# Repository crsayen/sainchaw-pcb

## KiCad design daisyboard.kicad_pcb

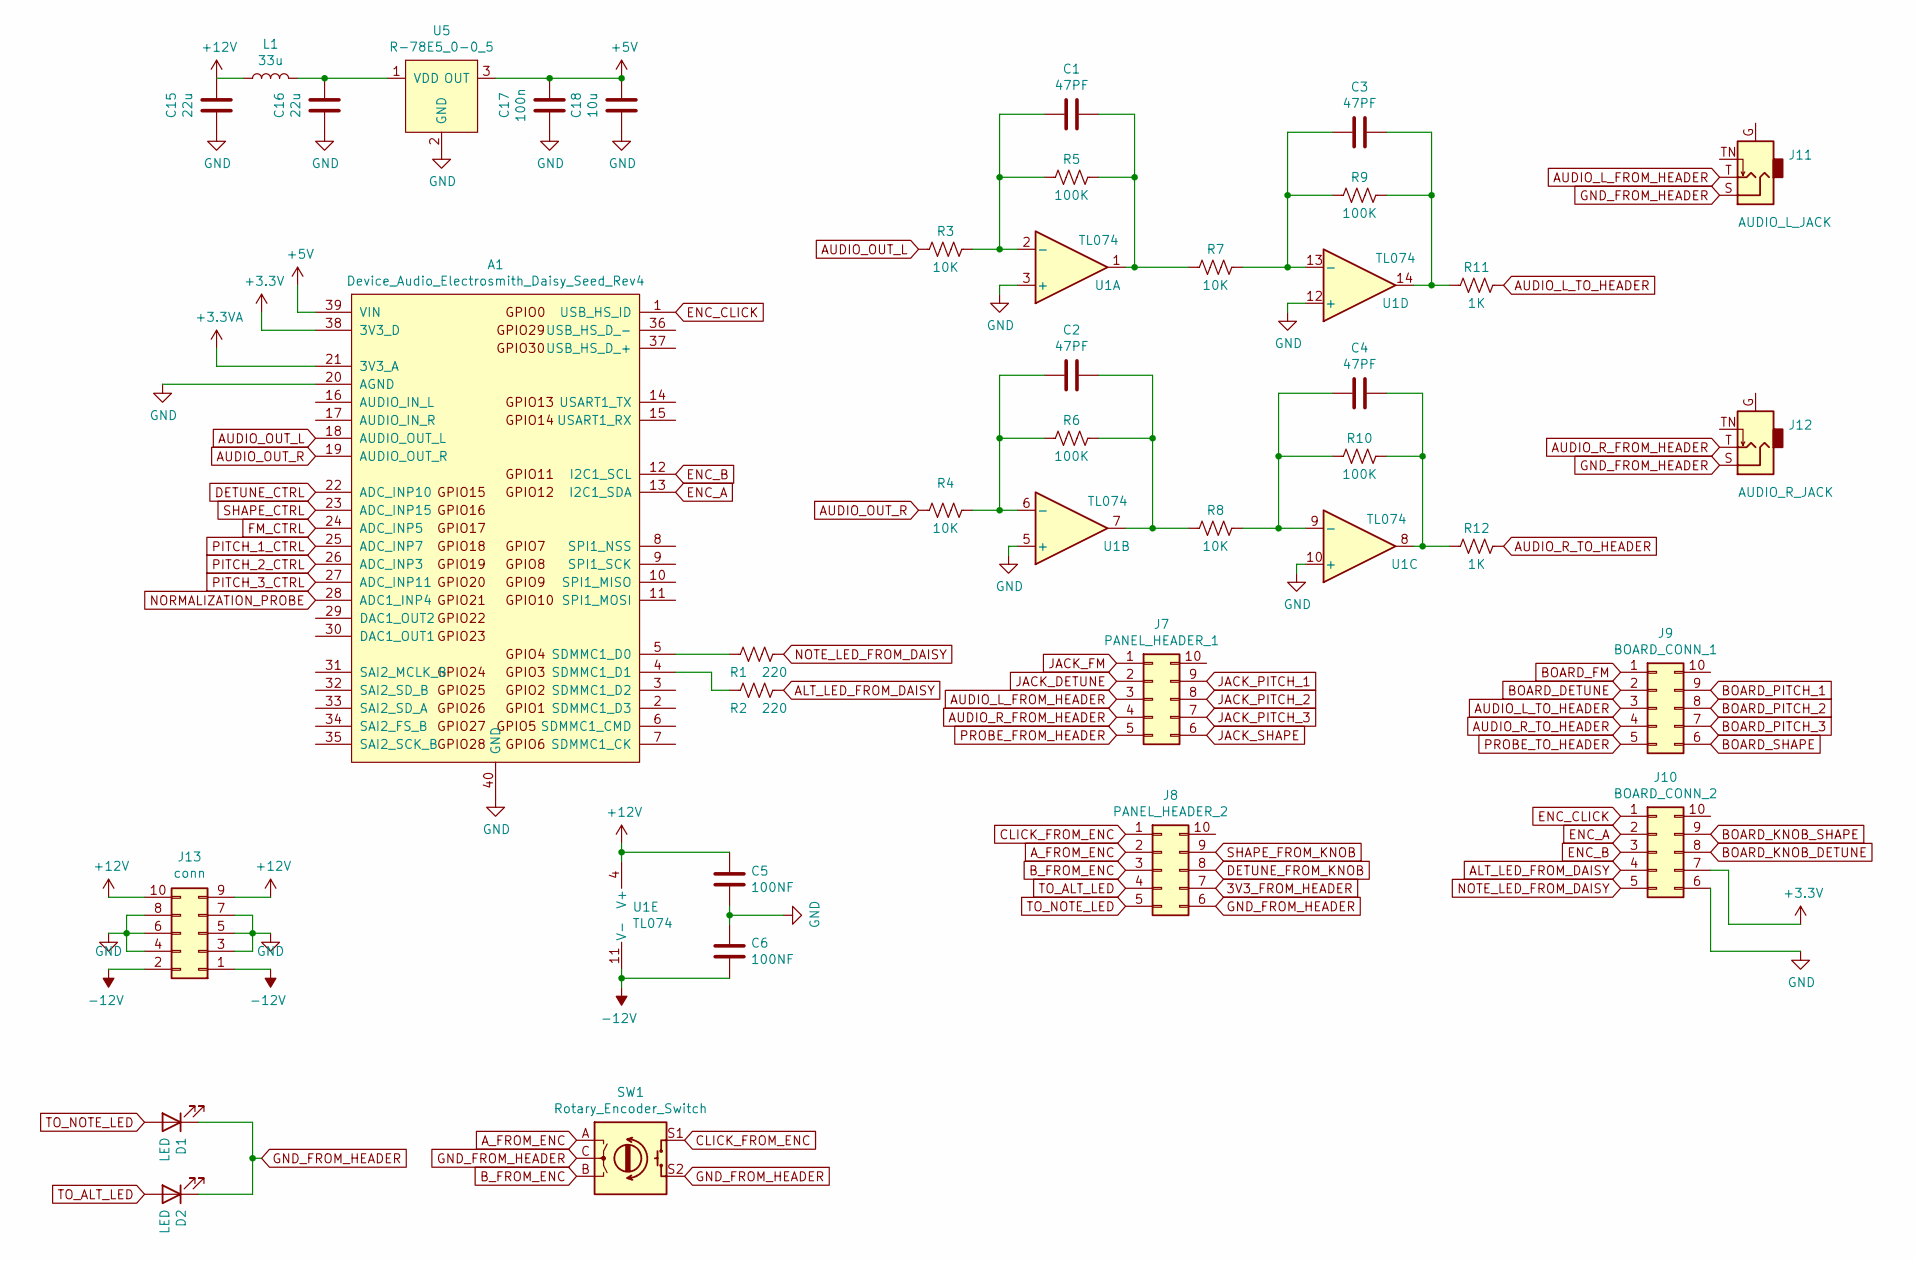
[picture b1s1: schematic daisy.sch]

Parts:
A1: Device_Audio_Electrosmith_Daisy_Seed_Rev4; Device_Audio_Electrosmith_Daisy_Seed
C1, C2, C3, C4: 47PF; C_0805_2012Metric
C5, C6: 100NF; C_0805_2012Metric
C15, C16: 22u; C_0805_2012Metric
C17: 100n; C_0805_2012Metric
C18: 10u; C_0805_2012Metric
D1, D2: LED; LED_D3.0mm
J7: PANEL_HEADER_1; PinHeader_1x10_P2.54mm_Vertical
J8: PANEL_HEADER_2; PinHeader_1x10_P2.54mm_Vertical
J9: BOARD_CONN_1; PinSocket_1x10_P2.54mm_Vertical
J10: BOARD_CONN_2; PinSocket_1x10_P2.54mm_Vertical
J11: AUDIO_L_JACK; Jack_3.5mm_QingPu_WQP-PJ398SM_Vertical_CircularHoles
J12: AUDIO_R_JACK; Jack_3.5mm_QingPu_WQP-PJ398SM_Vertical_CircularHoles
J13: conn; PinHeader_2x05_P2.54mm_Vertical
L1: 33u
R1, R2: 220; R_0805_2012Metric
R3, R4, R7, R8: 10K; R_0805_2012Metric
R5, R6, R9, R10: 100K; R_0805_2012Metric
R11, R12: 1K; R_0805_2012Metric
SW1: Rotary_Encoder_Switch; RotaryEncoder_Alps_EC11E-Switch_Vertical_H20mm
U1: TL074; TSSOP-14_4.4x5mm_P0.65mm
U5: R-78E5_0-0_5; SIP-3_P2.54mm; MPN R-78E5.0-0.5; Digi-Key_PN 945-1648-5-ND

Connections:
+3V3: A1.38 (3V3_D), J10.7; also elsewhere on the board
+5V: A1.39 (VIN), C17.1, C18.1, U5.3 (OUT)
+12V: C5.1, C15.1, J13.9, J13.10, L1.1, U1.4 (V+)
-12V: C6.2, J13.1, J13.2, U1.11 (V-); also elsewhere on the board
ALT_LED_FROM_DAISY: J10.4, R2.1
AUDIO_L_FROM_HEADER: J7.3, J11.T
AUDIO_L_TO_HEADER: J9.3, R11.1
AUDIO_OUT_L: A1.18 (AUDIO_OUT_L), R3.2
AUDIO_OUT_R: A1.19 (AUDIO_OUT_R), R4.2
AUDIO_R_FROM_HEADER: J7.4, J12.T
AUDIO_R_TO_HEADER: J9.4, R12.1
A_FROM_ENC: J8.2, SW1.A
BOARD_DETUNE: J9.2; also elsewhere on the board
BOARD_FM: J9.1; also elsewhere on the board
BOARD_KNOB_DETUNE: J10.8; also elsewhere on the board
BOARD_KNOB_SHAPE: J10.9; also elsewhere on the board
BOARD_PITCH_1: J9.9; also elsewhere on the board
BOARD_PITCH_2: J9.8; also elsewhere on the board
BOARD_PITCH_3: J9.7; also elsewhere on the board
BOARD_SHAPE: J9.6; also elsewhere on the board
B_FROM_ENC: J8.3, SW1.B
CLICK_FROM_ENC: J8.1, SW1.S1
DETUNE_CTRL: A1.22 (ADC_INP10); also elsewhere on the board
DETUNE_FROM_KNOB: J8.8; also elsewhere on the board
ENC_A: A1.13 (I2C1_SDA), J10.2
ENC_B: A1.12 (I2C1_SCL), J10.3
ENC_CLICK: A1.1 (USB_HS_ID), J10.1
FM_CTRL: A1.24 (ADC_INP5); also elsewhere on the board
JACK_DETUNE: J7.2; also elsewhere on the board
JACK_FM: J7.1; also elsewhere on the board
JACK_PITCH_1: J7.9; also elsewhere on the board
JACK_PITCH_2: J7.8; also elsewhere on the board
JACK_PITCH_3: J7.7; also elsewhere on the board
JACK_SHAPE: J7.6; also elsewhere on the board
NORMALIZATION_PROBE: A1.28 (ADC1_INP4), J9.5; also elsewhere on the board
NOTE_LED_FROM_DAISY: J10.5, R1.1
unnamed: A1.4 (SDMMC1_D1), R2.2
unnamed: A1.5 (SDMMC1_D0), R1.2
unnamed: C1.1, R5.1, R7.2, U1.1
unnamed: C1.2, R3.1, R5.2, U1.2 (-)
unnamed: C2.1, R6.1, R8.2, U1.7
unnamed: C2.2, R4.1, R6.2, U1.6 (-)
unnamed: C3.1, R9.1, R11.2, U1.14
unnamed: C3.2, R7.1, R9.2, U1.13 (-)
unnamed: C4.1, R10.1, R12.2, U1.8
unnamed: C4.2, R8.1, R10.2, U1.9 (-)
unnamed: C16.1, L1.2, U5.1 (VDD)
PITCH_1_CTRL: A1.25 (ADC_INP7); also elsewhere on the board
PITCH_2_CTRL: A1.26 (ADC_INP3); also elsewhere on the board
PITCH_3_CTRL: A1.27 (ADC_INP11); also elsewhere on the board
PROBE_FROM_HEADER: J7.5; also elsewhere on the board
SHAPE_CTRL: A1.23 (ADC_INP15); also elsewhere on the board
SHAPE_FROM_KNOB: J8.9; also elsewhere on the board
TO_ALT_LED: D2.2 (A), J8.4
TO_NOTE_LED: D1.2 (A), J8.5

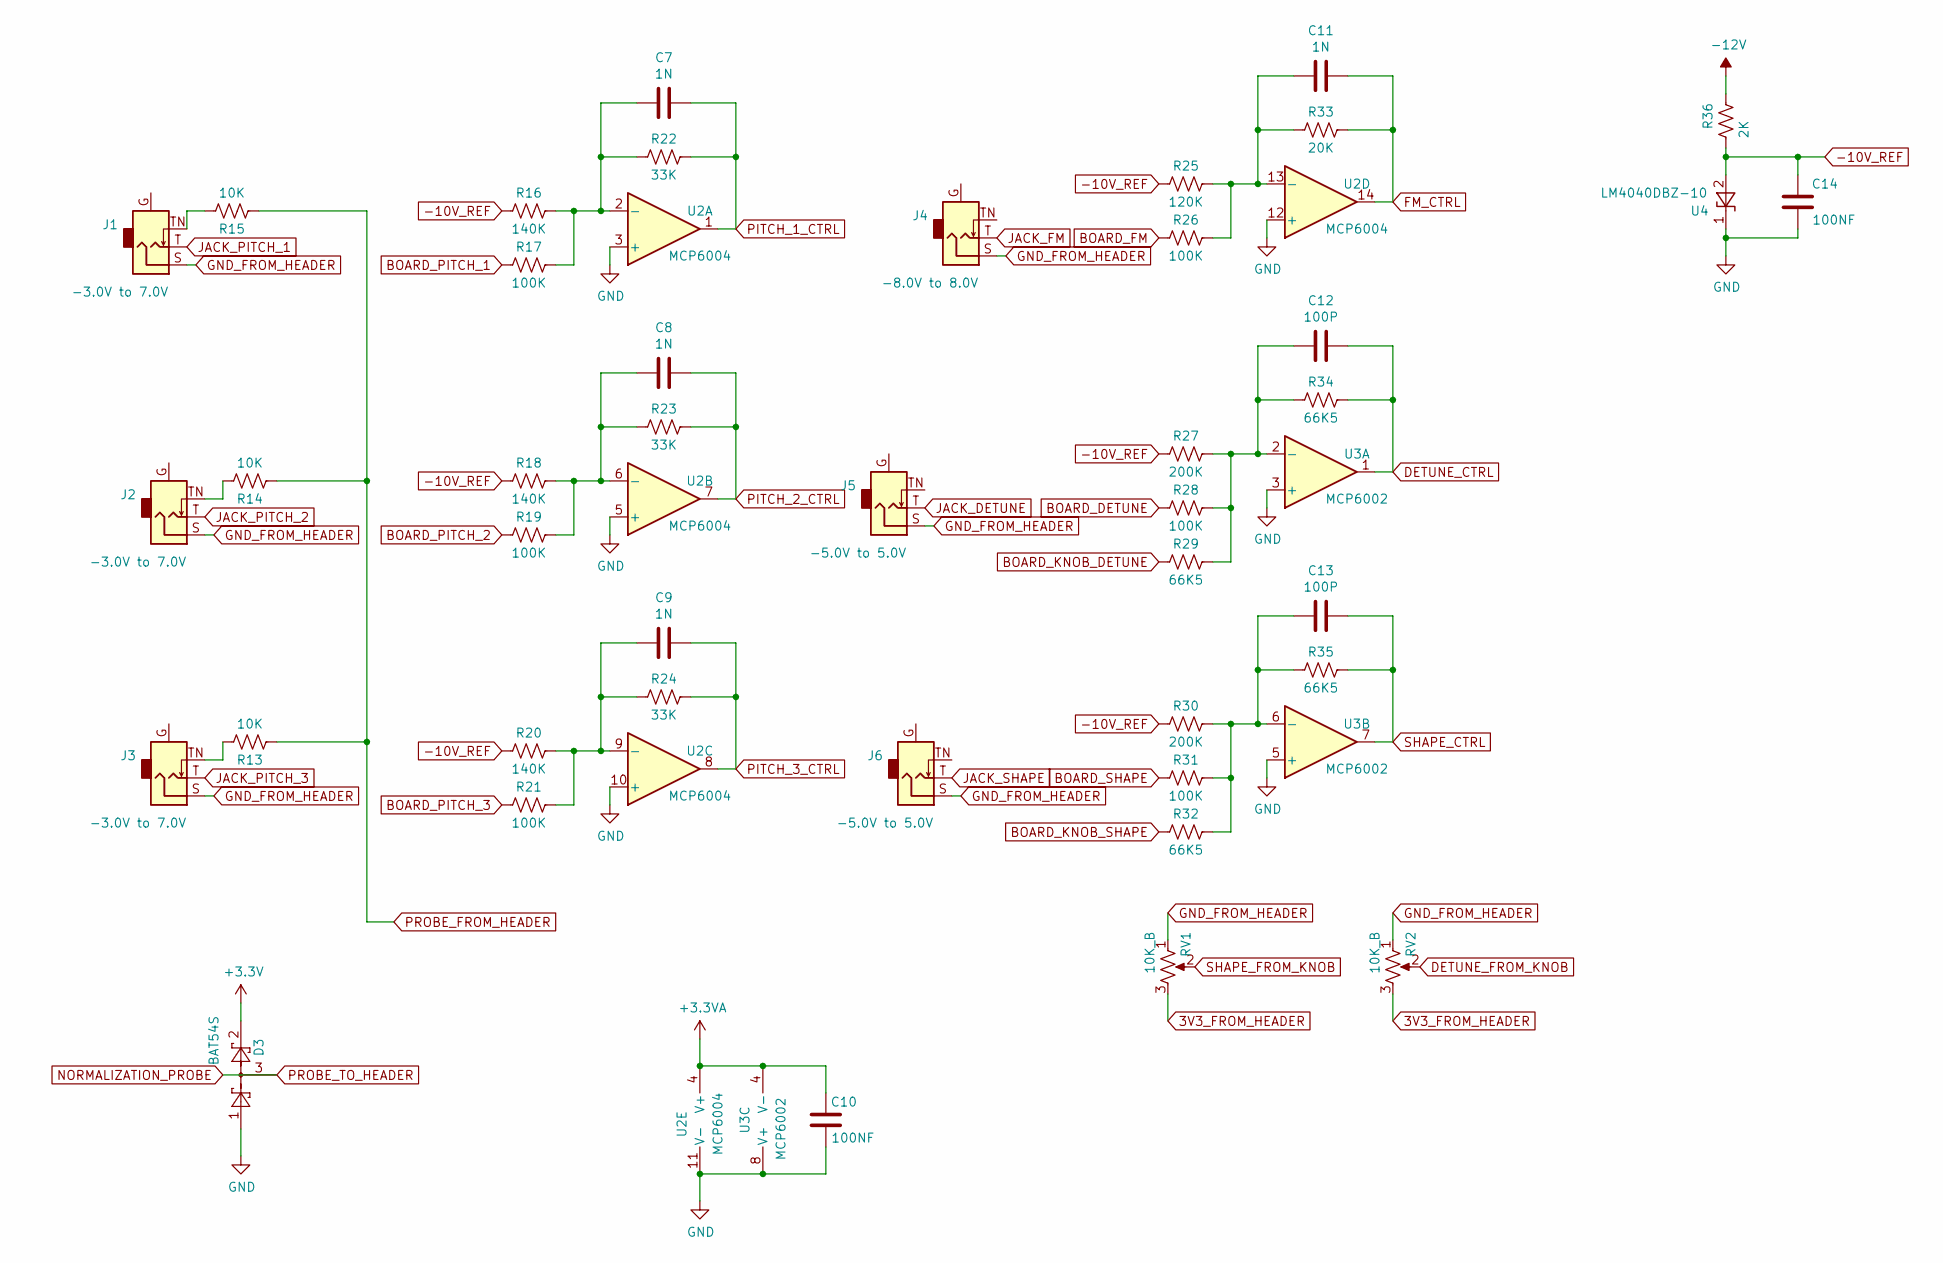
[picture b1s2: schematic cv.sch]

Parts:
C7, C8, C9, C11: 1N; C_0805_2012Metric
C10, C14: 100NF; C_0805_2012Metric
C12, C13: 100P; C_0805_2012Metric
D3: BAT54S; SOT-23
J1, J2, J3: -3.0V to 7.0V; Jack_3.5mm_QingPu_WQP-PJ398SM_Vertical_CircularHoles
J4: -8.0V to 8.0V; Jack_3.5mm_QingPu_WQP-PJ398SM_Vertical_CircularHoles
J5, J6: -5.0V to 5.0V; Jack_3.5mm_QingPu_WQP-PJ398SM_Vertical_CircularHoles
R13, R14, R15: 10K; R_0805_2012Metric
R16, R18, R20: 140K; R_0805_2012Metric
R17, R19, R21, R26, R28, R31: 100K; R_0805_2012Metric
R22, R23, R24: 33K; R_0805_2012Metric
R25: 120K; R_0805_2012Metric
R27, R30: 200K; R_0805_2012Metric
R29, R32, R34, R35: 66K5; R_0805_2012Metric
R33: 20K; R_0805_2012Metric
R36: 2K; R_0805_2012Metric
RV1, RV2: 10K_B; Potentiometer_Alpha_RD901F-40-00D_Single_Vertical
U2: MCP6004; TSSOP-14_4.4x5mm_P0.65mm
U3: MCP6002; SOIC-8_3.9x4.9mm_P1.27mm
U4: LM4040DBZ-10; SOT-23

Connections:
+3V3: D3.2; also elsewhere on the board
-10V_REF: C14.2, R16.2, R18.2, R20.2, R25.2, R27.2, R30.2, R36.2, U4.2 (A)
-12V: R36.1; also elsewhere on the board
BOARD_DETUNE: R28.2; also elsewhere on the board
BOARD_FM: R26.2; also elsewhere on the board
BOARD_KNOB_DETUNE: R29.2; also elsewhere on the board
BOARD_KNOB_SHAPE: R32.2; also elsewhere on the board
BOARD_PITCH_1: R17.2; also elsewhere on the board
BOARD_PITCH_2: R19.2; also elsewhere on the board
BOARD_PITCH_3: R21.2; also elsewhere on the board
BOARD_SHAPE: R31.2; also elsewhere on the board
DETUNE_CTRL: C12.1, R34.1, U3.1; also elsewhere on the board
DETUNE_FROM_KNOB: RV2.2; also elsewhere on the board
FM_CTRL: C11.1, R33.1, U2.14; also elsewhere on the board
JACK_DETUNE: J5.T; also elsewhere on the board
JACK_FM: J4.T; also elsewhere on the board
JACK_PITCH_1: J1.T; also elsewhere on the board
JACK_PITCH_2: J2.T; also elsewhere on the board
JACK_PITCH_3: J3.T; also elsewhere on the board
JACK_SHAPE: J6.T; also elsewhere on the board
NORMALIZATION_PROBE: D3.3; also elsewhere on the board
unnamed: C7.2, R16.1, R17.1, R22.2, U2.2 (-)
unnamed: C8.2, R18.1, R19.1, R23.2, U2.6 (-)
unnamed: C9.2, R20.1, R21.1, R24.2, U2.9 (-)
unnamed: C11.2, R25.1, R26.1, R33.2, U2.13 (-)
unnamed: C12.2, R27.1, R28.1, R29.1, R34.2, U3.2 (-)
unnamed: C13.2, R30.1, R31.1, R32.1, R35.2, U3.6 (-)
unnamed: J1.TN, R15.1
unnamed: J2.TN, R14.1
unnamed: J3.TN, R13.1
PITCH_1_CTRL: C7.1, R22.1, U2.1; also elsewhere on the board
PITCH_2_CTRL: C8.1, R23.1, U2.7; also elsewhere on the board
PITCH_3_CTRL: C9.1, R24.1, U2.8; also elsewhere on the board
PROBE_FROM_HEADER: R13.2, R14.2, R15.2; also elsewhere on the board
SHAPE_CTRL: C13.1, R35.1, U3.7; also elsewhere on the board
SHAPE_FROM_KNOB: RV1.2; also elsewhere on the board

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
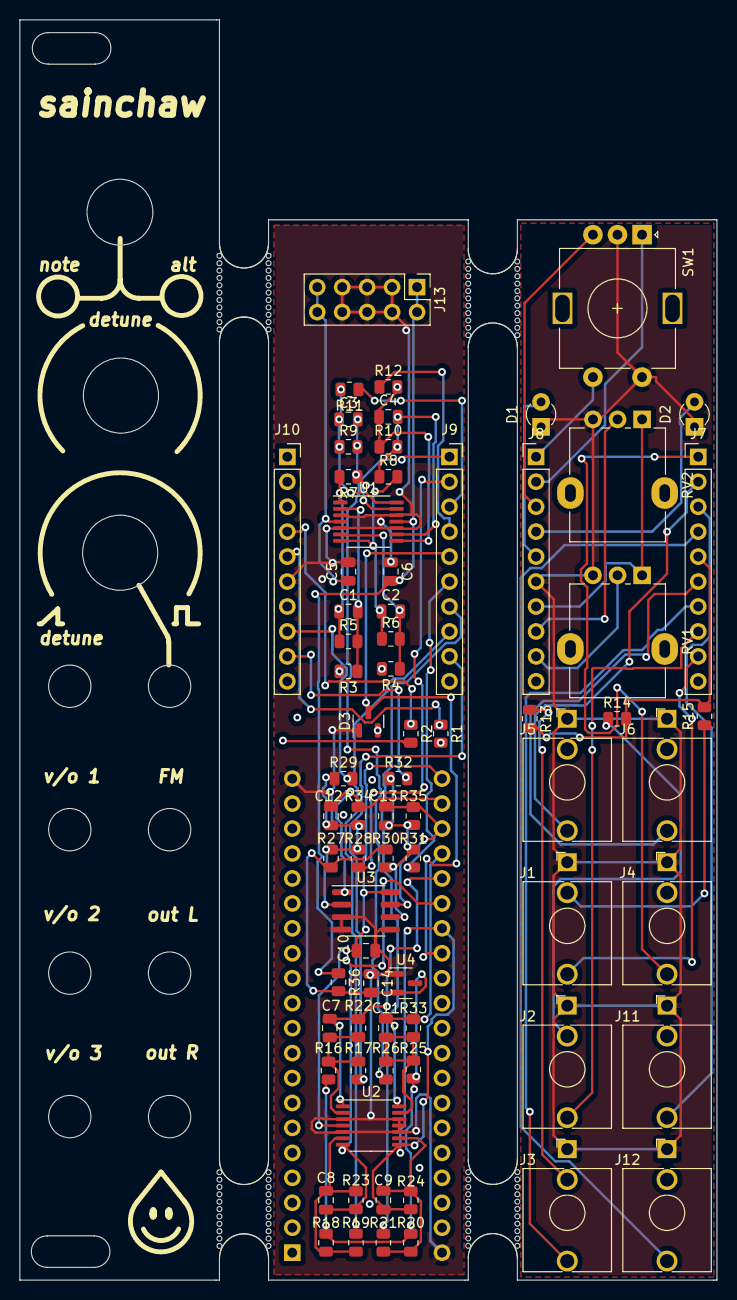
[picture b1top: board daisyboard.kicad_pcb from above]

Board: 4 copper layers, 71.0 x 128.3 mm, 78 parts (1 on the bottom side), 67 nets.

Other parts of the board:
mouse-bite-5mm-slot, mouse-bite-5mm-slot#2, mouse-bite-5mm-slot#3, mouse-bite-5mm-slot#4: VAL**; mouse-bite-5mm-slot

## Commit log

2022-03-06 init
